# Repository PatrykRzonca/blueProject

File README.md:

# blueProject
It is a repository for blue project which will include 2 sub projects

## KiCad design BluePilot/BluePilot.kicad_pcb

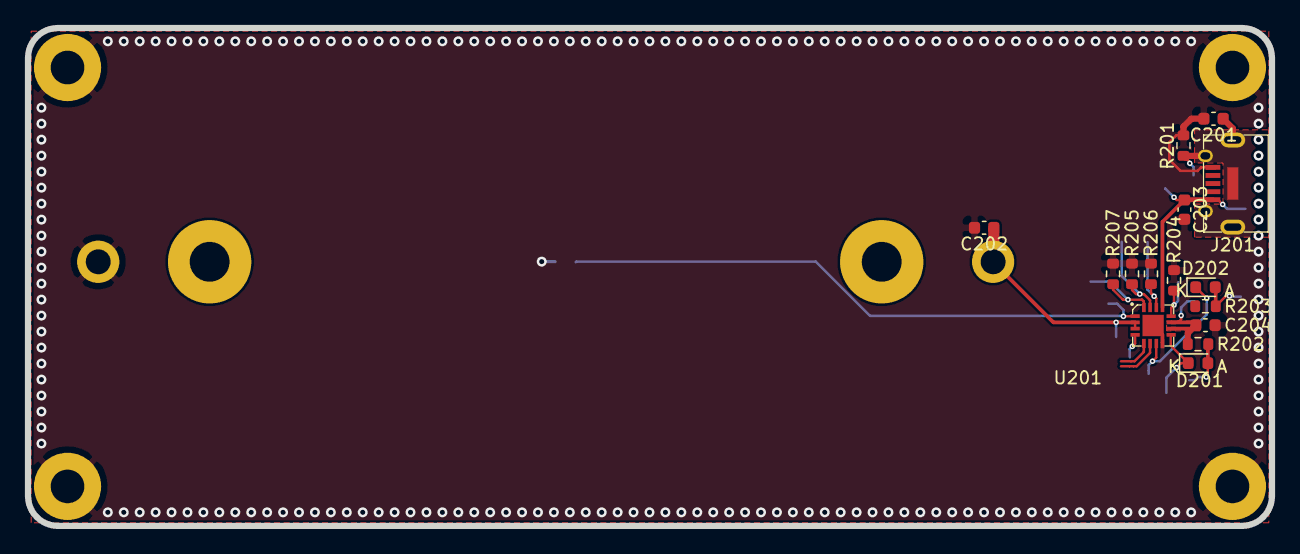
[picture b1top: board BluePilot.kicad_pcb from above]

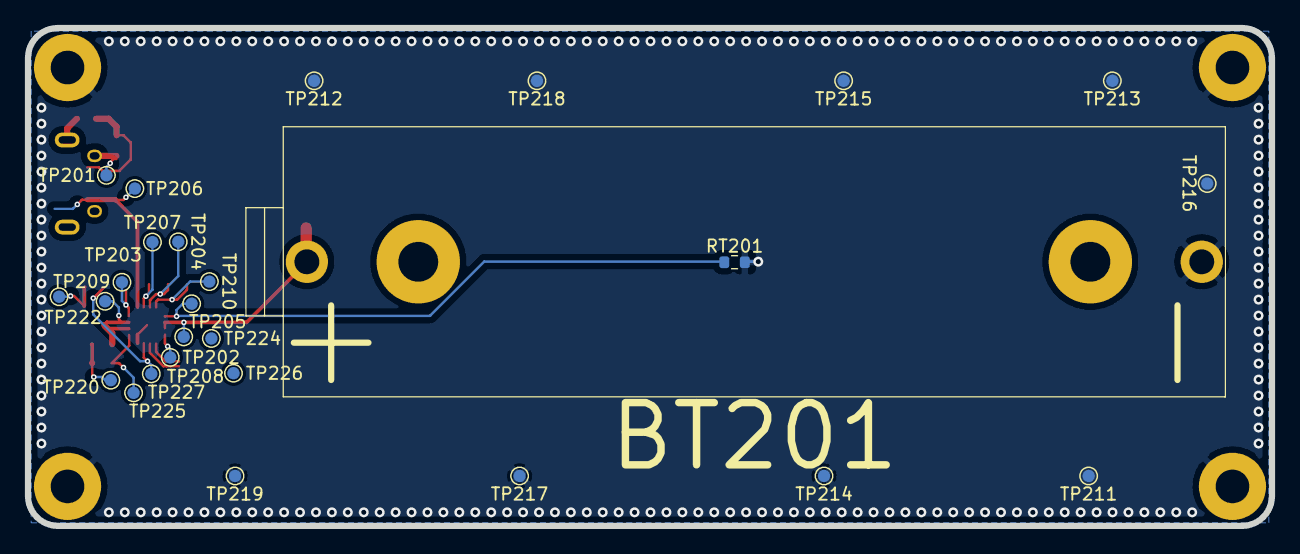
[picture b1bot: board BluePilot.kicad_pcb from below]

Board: 4 copper layers, 99.9 x 40.0 mm, 46 parts (27 on the bottom side), 17 nets.

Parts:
BT201: BHC-18650-1P
C201: CL10B472KC8WPNC
C202, C203, C204: CL10A475KP8NNNC
D201, D202: KB_DELPS2.12-QHRI-24-Z555-10-S
H201, H202, H203, H204: MountingHole_Pad; MountingHole_2.7mm_Pad
J201: UJ2-MIBH2-4-SMT-TR
R201: RC0603FR-071ML
R202, R203: CRGCQ0603F150R
R204, R205, R206, R207: R; R_0603_1608Metric
RT201: ERT-J1VR103J
TP201, TP202, TP203, TP204, TP205, TP206, TP207, TP208, TP209, TP210, TP211, TP212, TP213, TP214, TP215, TP216, TP217, TP218, TP219, TP220, TP222, TP224, TP225, TP226, TP227: TestPoint; TestPoint_Pad_D1.0mm
U201: BQ24232HRGTR

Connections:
/PowerSection/EN1: TP224.1, U201.6
/PowerSection/EN2: TP226.1, U201.5
/PowerSection/ILIM: R204.2, TP203.1, U201.12
/PowerSection/ISET: R207.2, TP210.1, U201.16
/PowerSection/ITERM: R205.2, TP204.1, U201.15
/PowerSection/TMR: R206.2, TP207.1, U201.14
/PowerSection/TS_sens: RT201.1, TP205.1, U201.1
/PowerSection/V_bat: BT201.1, C202.1, TP202.1, U201.2, U201.3
/PowerSection/V_charger: C203.1, J201.1, TP206.1, U201.13
/PowerSection/V_out: C204.1, R202.2, R203.2, TP209.1, U201.10, U201.11
/PowerSection/nCE_enable: TP208.1, U201.4
/PowerSection/~CHG: D201.1, TP225.1, U201.9
/PowerSection/~PGOOD: D202.1, TP227.1, U201.7
GND: BT201.2, C201.2, C202.2, C203.2, C204.2, H201.1, H202.1, H203.1, H204.1, J201.5, R201.2, R204.1, R205.1, R206.1, R207.1, RT201.2, TP211.1, TP212.1, TP213.1, TP214.1, TP215.1, TP216.1, TP217.1, TP218.1, TP219.1, U201.8, U201.17
unnamed: C201.1, J201.6, R201.1, TP201.1
unnamed: D201.2, R202.1, TP220.1
unnamed: D202.2, R203.1, TP222.1
